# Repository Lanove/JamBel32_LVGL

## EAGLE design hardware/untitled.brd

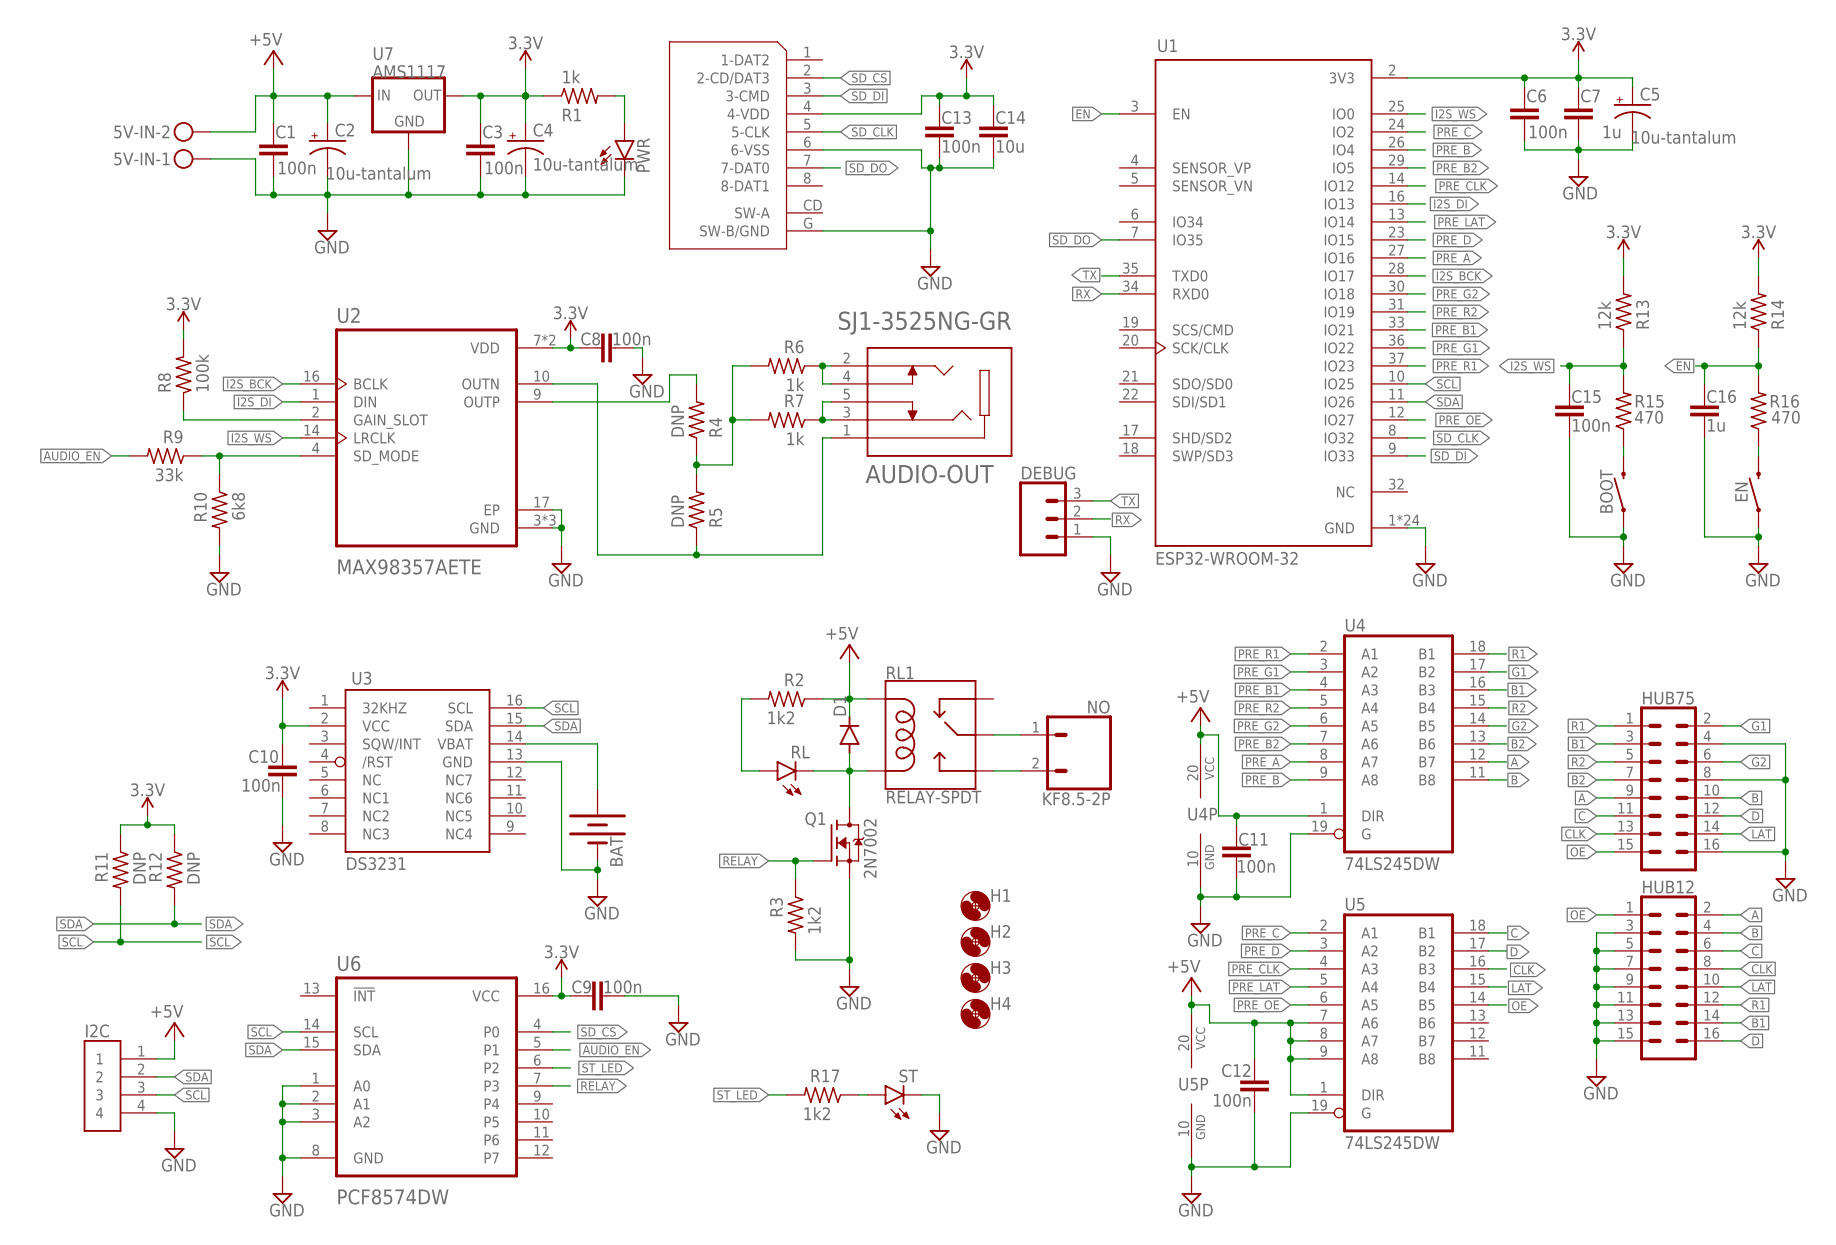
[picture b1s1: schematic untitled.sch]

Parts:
5V-IN: MKDSN1,5/2-5,08
AUDIO-OUT: SJ1-3525NG-GR; CUI_SJ1-3525NG-GR
BAT: BATTERY-20MM_PTH_KIT; BATTCOM_20MM_PTH_KIT
BOOT: MOMENTARY-SWITCH-SPST-SMD-6.0X3.5MM; TACTILE_SWITCH_SMD_6.0X3.5MM
C1, C3, C6, C8, C9, C10, C11, C12, C13, C15: 100n; C0603K
C2, C4, C5: 10u-tantalum; CT3528
C7, C16: 1u; C0603K
C14: 10u; C0603K
D1: DIODE-DO-214AC; DO-214AC
DEBUG: CONN_03; 1X03
EN: MOMENTARY-SWITCH-SPST-SMD-6.0X3.5MM; TACTILE_SWITCH_SMD_6.0X3.5MM
H1, H2, H3, H4: MOUNT-HOLE3.2; 3,2
HUB12, HUB75: CONN_08X2_SHROUD; 2X8-SHROUDED_LOCK
I2C: B4B-XH-A(LF)(SN); JST_B4B-XH-A(LF)(SN)
NO: KF8.5-2P; KF7.62
PWR: LEDCHIP-LED0805; CHIP-LED0805
Q1: 2N7002; SOT95P240X111-3N
R1, R6, R7: 1k; R0603
R2, R3, R17: 1k2; R0603
R4, R5, R11, R12: DNP; R0603
R8: 100k; R0603
R9: 33k; R0603
R10: 6k8; R0603
R13, R14: 12k; R0603
R15, R16: 470; R0603
RL: LEDCHIP-LED0805; CHIP-LED0805
RL1: RELAY-SPDT; RELAY_G5LE
ST: LEDCHIP-LED0805; CHIP-LED0805
U1: ESP32-WROOM-32; MODULE_ESP32-WROOM-32
U2: MAX98357AETE; QFN50P300X300X80-17N
U3: DS3231/SO; SO16W
U4, U5: 74LS245DW; SO20W
U6: PCF8574DW; SOIC127P1030X265-16N
U7: AMS1117; SOT89R
μSD: 112J-TDAR-R01

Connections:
3.3V: C3.1, C4.+, C5.+, C6.1, C7.1, C8.1, C9.1, C10.2, C13.2, C14.2, R1.1, R8.2, R11.1, R12.1, R13.2, R14.2, U1.2 (3V3), U2.7 (VDD), U2.8 (VDD), U3.2 (VCC), U6.16 (VCC), U7.3 (OUT), U7.4 (OUT), μSD.4 (4-VDD)
+5V: 5V-IN.2, C1.1, C2.+, C11.1, C12.2, D1.C, I2C.1, R2.1, RL1.2 (COIL1), U4.1 (DIR), U4.20 (VCC), U5.1 (DIR), U5.7 (A6), U5.8 (A7), U5.9 (A8), U5.20 (VCC), U7.1 (IN)
A: HUB12.2, HUB75.9, U4.12 (B7)
AUDIO_EN: R9.2, U6.5 (P1)
B: HUB12.4, HUB75.10, U4.11 (B8)
B1: HUB12.14, HUB75.3, U4.16 (B3)
B2: HUB75.7, U4.13 (B6)
C: HUB12.6, HUB75.11, U5.18 (B1)
CLK: HUB12.8, HUB75.13, U5.16 (B3)
D: HUB12.16, HUB75.12, U5.17 (B2)
EN: C16.2, R14.1, R16.2, U1.3 (EN)
G1: HUB75.2, U4.17 (B2)
G2: HUB75.6, U4.14 (B5)
GND: 5V-IN.1, BAT.2 (-), BOOT.1, C1.2, C2.-, C3.2, C4.-, C5.-, C6.2, C7.2, C8.2, C9.2, C10.1, C11.2, C12.1, C13.1, C14.1, C15.1, C16.1, DEBUG.1, EN.1, HUB12.3, HUB12.5, HUB12.7, HUB12.9, HUB12.11, HUB12.13, HUB12.15, HUB75.4, HUB75.8, HUB75.16, I2C.4, PWR.C, Q1.2 (S), R3.2, R10.2, ST.C, U1.1 (GND), U1.15 (GND), U1.38 (GND), U1.39_1 (GND), U1.39_2 (GND), U1.39_3 (GND), U1.39_4 (GND), U1.39_5 (GND), U1.39_6 (GND), U1.39_7 (GND), U1.39_8 (GND), U1.39_9 (GND), U1.39_10 (GND), U1.39_11 (GND), U1.39_12 (GND), U1.39_13 (GND), U1.39_14 (GND), U1.39_15 (GND), U1.39_16 (GND), U1.39_17 (GND), U1.39_18 (GND), U1.39_19 (GND), U1.39_20 (GND), U1.39_21 (GND), U2.3 (GND), U2.11 (GND), U2.15 (GND), U2.17 (EP), U3.13 (GND), U4.10 (GND), U4.19 (G), U5.10 (GND), U5.19 (G), U6.1 (A0), U6.2 (A1), U6.3 (A2), U6.8 (GND), U7.2 (GND), μSD.6 (6-VSS), μSD.G (SW-B/GND)
I2S_BCK: U1.28 (IO17), U2.16 (BCLK)
I2S_DI: U1.16 (IO13), U2.1 (DIN)
I2S_WS: C15.2, R13.1, R15.2, U1.25 (IO0), U2.14 (LRCLK)
LAT: HUB12.10, HUB75.14, U5.15 (B4)
unnamed: NO.1, RL1.1 (MAIN)
unnamed: NO.2, RL1.3 (NO)
unnamed: R4.2, U2.9 (OUTP)
unnamed: PWR.A, R1.2
unnamed: AUDIO-OUT.1, R5.1, U2.10 (OUTN)
unnamed: R4.1, R5.2, R6.2, R7.2
unnamed: R8.1, U2.2 (GAIN_SLOT)
unnamed: AUDIO-OUT.3, AUDIO-OUT.5, R7.1
unnamed: R9.1, R10.1, U2.4 (SD_MODE)
unnamed: AUDIO-OUT.2, AUDIO-OUT.4, R6.1
unnamed: BAT.1 (+), U3.14 (VBAT)
unnamed: EN.2, R16.1
unnamed: BOOT.2, R15.1
unnamed: R17.1, ST.A
unnamed: D1.A, Q1.3 (D), RL.C, RL1.5 (COIL2)
unnamed: R2.2, RL.A
OE: HUB12.1, HUB75.15, U5.14 (B5)
PRE_A: U1.27 (IO16), U4.8 (A7)
PRE_B: U1.26 (IO4), U4.9 (A8)
PRE_B1: U1.33 (IO21), U4.4 (A3)
PRE_B2: U1.29 (IO5), U4.7 (A6)
PRE_C: U1.24 (IO2), U5.2 (A1)
PRE_CLK: U1.14 (IO12), U5.4 (A3)
PRE_D: U1.23 (IO15), U5.3 (A2)
PRE_G1: U1.36 (IO22), U4.3 (A2)
PRE_G2: U1.30 (IO18), U4.6 (A5)
PRE_LAT: U1.13 (IO14), U5.5 (A4)
PRE_OE: U1.12 (IO27), U5.6 (A5)
PRE_R1: U1.37 (IO23), U4.2 (A1)
PRE_R2: U1.31 (IO19), U4.5 (A4)
R1: HUB12.12, HUB75.1, U4.18 (B1)
R2: HUB75.5, U4.15 (B4)
RELAY: Q1.1 (G), R3.1, U6.7 (P3)
RX: DEBUG.2, U1.34 (RXD0)
SCL: I2C.3, R11.2, U1.10 (IO25), U3.16 (SCL), U6.14 (SCL)
SDA: I2C.2, R12.2, U1.11 (IO26), U3.15 (SDA), U6.15 (SDA)
SD_CLK: U1.8 (IO32), μSD.5 (5-CLK)
SD_CS: U6.4 (P0), μSD.2 (2-CD/DAT3)
SD_DI: U1.9 (IO33), μSD.3 (3-CMD)
SD_DO: U1.7 (IO35), μSD.7 (7-DAT0)
ST_LED: R17.2, U6.6 (P2)
TX: DEBUG.3, U1.35 (TXD0)

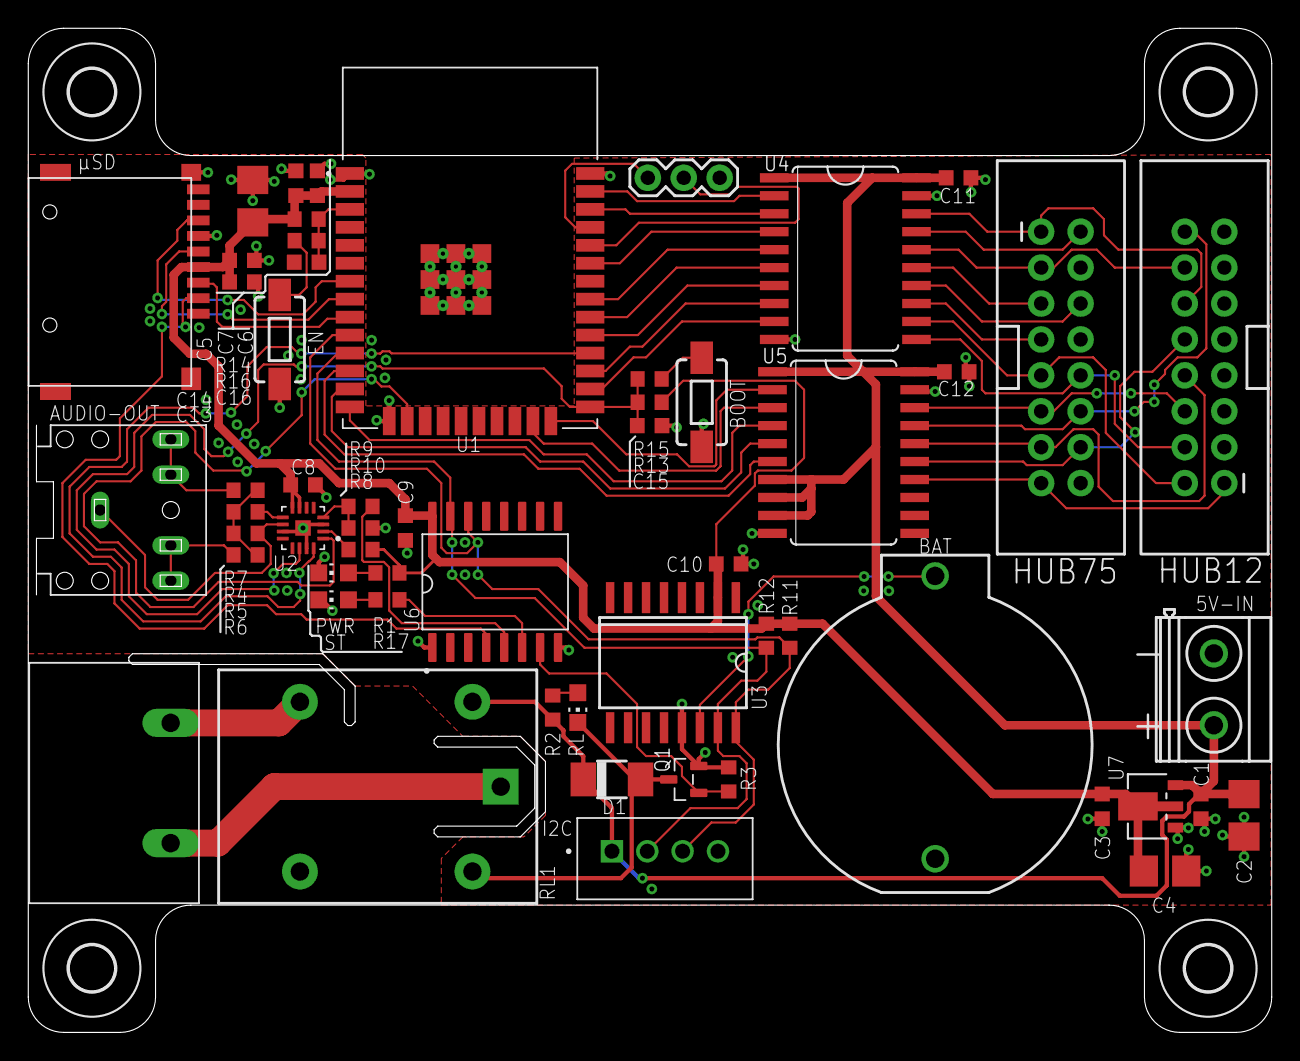
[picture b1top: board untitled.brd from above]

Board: 2 copper layers, 87.9 x 71.0 mm, 61 parts (0 on the bottom side), 60 nets.

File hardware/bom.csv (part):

"Part";"Value";"Device";"Package";"Description";"AVAILABILITY";"CUI_PURCHASE_URL";"DESCRIPTION";"MANUFACTURER";"MAXIMUM_PACKAGE_HEIGHT";"MF";"MP";"PACKAGE";"PARTREV";"POPULARITY";"PRICE";"PROD_ID";"PURCHASE-URL";"SF_SKU";"SPICEPREFIX";"STANDARD";"VALUE";
"5V-IN";"";"MKDSN1,5/2-5,08";"MKDSN1,5/2-5,08";"MKDSN 1,5/ 2-5,08 Printklemme";"";"";"";"";"";"";"";"";"";"14";"";"";"";"";"";"";"";
"AUDIO-OUT";"SJ1-3525NG-GR";"SJ1-3525NG-GR";"CUI_SJ1-3525NG-GR";"3.5 mm Right-Angle Stereo Jack, 5 Pin PCB Mount, Isolated Ground, Green Check availability";"In Stock";"https://www.cuidevices.com/product/interconnect/connectors/a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";"3.5 mm, Stereo, Right Angle, Through Hole, Isolated Ground, 3 Conductors, 0~2 Internal Switches, Audio Jack Connector";"";"";"CUI Devices";"SJ1-3525NG-GR";"None";"";"";"None";"";"https://pricing.snapeda.com/search/part/SJ1-3525NG-GR/?ref=eda";"";"";"";"";
"BAT";"";"BATTERY-20MM_PTH_KIT";"BATTCOM_20MM_PTH_KIT";"Battery - Single Cell";"";"";"";"";"";"";"";"";"";"";"";"";"";"";"";"";"";
"BOOT";"";"MOMENTARY-SWITCH-SPST-SMD-6.0X3.5MM";"TACTILE_SWITCH_SMD_6.0X3.5MM";"Momentary Switch (Pushbutton) - SPST";"";"";"";"";"";"";"";"";"";"";"";"SWCH-14278";"";"COM-08229";"";"";"";
"C1";"100n";"C-EUC0603K";"C0603K";"CAPACITOR, European symbol";"";"";"";"";"";"";"";"";"";"30";"";"";"";"";"C";"";"";
"C2";"10u-tantalum";"CPOL-USCT3528";"CT3528";"POLARIZED CAPACITOR, American symbol";"";"";"";"";"";"";"";"";"";"2";"";"";"";"";"C";"";"";
"C3";"100n";"C-EUC0603K";"C0603K";"CAPACITOR, European symbol";"";"";"";"";"";"";"";"";"";"30";"";"";"";"";"C";"";"";
"C4";"10u-tantalum";"CPOL-USCT3528";"CT3528";"POLARIZED CAPACITOR, American symbol";"";"";"";"";"";"";"";"";"";"2";"";"";"";"";"C";"";"";
"C5";"10u-tantalum";"CPOL-USCT3528";"CT3528";"POLARIZED CAPACITOR, American symbol";"";"";"";"";"";"";"";"";"";"2";"";"";"";"";"C";"";"";
"C6";"100n";"C-EUC0603K";"C0603K";"CAPACITOR, European symbol";"";"";"";"";"";"";"";"";"";"30";"";"";"";"";"C";"";"";
"C7";"1u";"C-EUC0603K";"C0603K";"CAPACITOR, European symbol";"";"";"";"";"";"";"";"";"";"30";"";"";"";"";"C";"";"";
"C8";"100n";"C-EUC0603K";"C0603K";"CAPACITOR, European symbol";"";"";"";"";"";"";"";"";"";"30";"";"";"";"";"C";"";"";
"C9";"100n";"C-EUC0603K";"C0603K";"CAPACITOR, European symbol";"";"";"";"";"";"";"";"";"";"30";"";"";"";"";"C";"";"";
"C10";"100n";"C-EUC0603K";"C0603K";"CAPACITOR, European symbol";"";"";"";"";"";"";"";"";"";"30";"";"";"";"";"C";"";"";
"C11";"100n";"C-EUC0603K";"C0603K";"CAPACITOR, European symbol";"";"";"";"";"";"";"";"";"";"30";"";"";"";"";"C";"";"";
"C12";"100n";"C-EUC0603K";"C0603K";"CAPACITOR, European symbol";"";"";"";"";"";"";"";"";"";"30";"";"";"";"";"C";"";"";
"C13";"100n";"C-EUC0603K";"C0603K";"CAPACITOR, European symbol";"";"";"";"";"";"";"";"";"";"30";"";"";"";"";"C";"";"";
"C14";"10u";"C-EUC0603K";"C0603K";"CAPACITOR, European symbol";"";"";"";"";"";"";"";"";"";"30";"";"";"";"";"C";"";"";
"C15";"100n";"C-EUC0603K";"C0603K";"CAPACITOR, European symbol";"";"";"";"";"";"";"";"";"";"30";"";"";"";"";"C";"";"";
"C16";"1u";"C-EUC0603K";"C0603K";"CAPACITOR, European symbol";"";"";"";"";"";"";"";"";"";"30";"";"";"";"";"C";"";"";
"D1";"";"DIODE-DO-214AC";"DO-214AC";"DIODE";"";"";"";"";"";"";"";"";"";"25";"";"";"";"";"";"";"";
"DEBUG";"";"CONN_03";"1X03";"Multi connection point. Often used as Generic Header-pin footprint for 0.1 inch spaced/style header connections";"";"";"";"";"";"";"";"";"";"";"";"XXX-00000";"";"";"";"";"455-1750-1-ND";
"EN";"";"MOMENTARY-SWITCH-SPST-SMD-6.0X3.5MM";"TACTILE_SWITCH_SMD_6.0X3.5MM";"Momentary Switch (Pushbutton) - SPST";"";"";"";"";"";"";"";"";"";"";"";"SWCH-14278";"";"COM-08229";"";"";"";
"H1";"";"MOUNT-HOLE3.2";"3,2";"MOUNTING HOLE with drill center marker";"";"";"";"";"";"";"";"";"";"7";"";"";"";"";"";"";"";
"H2";"";"MOUNT-HOLE3.2";"3,2";"MOUNTING HOLE with drill center marker";"";"";"";"";"";"";"";"";"";"7";"";"";"";"";"";"";"";
"H3";"";"MOUNT-HOLE3.2";"3,2";"MOUNTING HOLE with drill center marker";"";"";"";"";"";"";"";"";"";"7";"";"";"";"";"";"";"";
"H4";"";"MOUNT-HOLE3.2";"3,2";"MOUNTING HOLE with drill center marker";"";"";"";"";"";"";"";"";"";"7";"";"";"";"";"";"";"";
"HUB12";"";"CONN_08X2_SHROUD";"2X8-SHROUDED_LOCK";"Multi connection point. Often used as Generic Header-pin footprint for 0.1 inch spaced/style header connections";"";"";"";"";"";"";"";"";"";"";"";"";"";"";"";"";"";
"HUB75";"";"CONN_08X2_SHROUD";"2X8-SHROUDED_LOCK";"Multi connection point. Often used as Generic Header-pin footprint for 0.1 inch spaced/style header connections";"";"";"";"";"";"";"";"";"";"";"";"";"";"";"X";"";"";
"I2C";"";"B4B-XH-A(LF)(SN)";"JST_B4B-XH-A(LF)(SN)";"XH Series 4 Position 2.5 mm Pitch Through Hole Crimp Top Entry Shrouded Header";"";"";"";" JST Sales America Inc";"";"";"";"";"NA";"";"";"";"";"";"";"Manufacturer Recommendation";"";
"NO";"KF8.5-2P";"KF7.62-2P";"KF7.62";"";"";"";"";"";"";"";"";"";"";"";"";"";"";"";"";"";"";
"PWR";"";"LEDCHIP-LED0805";"CHIP-LED0805";"LED";"";"";"";"";"";"";"";"";"";"68";"";"";"";"";"";"";"";
"Q1";"2N7002";"2N7002";"SOT95P240X111-3N";"N-Channel 60V 280mA (Ta) 350mW (Ta) Surface Mount SOT-23-3 (TO-236)  Check availability";"In Stock";"";" N-Channel 60V 280mA (Ta) 350mW (Ta) Surface Mount SOT-23-3 (TO-236) ";"";"";"ON Semiconductor";"2N7002";"SOT-23-3 ON Semiconductor";"";"";"None";"";"https://pricing.snapeda.com/search/part/2N7002/?ref=eda";"";"";"";"";
"R1";"1k";"R-US_R0603";"R0603";"RESISTOR, American symbol";"";"";"";"";"";"";"";"";"";"77";"";"";"";"";"R";"";"";
"R2";"1k2";"R-US_R0603";"R0603";"RESISTOR, American symbol";"";"";"";"";"";"";"";"";"";"77";"";"";"";"";"R";"";"";
"R3";"1k2";"R-US_R0603";"R0603";"RESISTOR, American symbol";"";"";"";"";"";"";"";"";"";"77";"";"";"";"";"R";"";"";
"R4";"DNP";"R-US_R0603";"R0603";"RESISTOR, American symbol";"";"";"";"";"";"";"";"";"";"77";"";"";"";"";"R";"";"";
"R5";"DNP";"R-US_R0603";"R0603";"RESISTOR, American symbol";"";"";"";"";"";"";"";"";"";"77";"";"";"";"";"R";"";"";
"R6";"1k";"R-US_R0603";"R0603";"RESISTOR, American symbol";"";"";"";"";"";"";"";"";"";"77";"";"";"";"";"R";"";"";
"R7";"1k";"R-US_R0603";"R0603";"RESISTOR, American symbol";"";"";"";"";"";"";"";"";"";"77";"";"";"";"";"R";"";"";
"R8";"100k";"R-US_R0603";"R0603";"RESISTOR, American symbol";"";"";"";"";"";"";"";"";"";"77";"";"";"";"";"R";"";"";
"R9";"33k";"R-US_R0603";"R0603";"RESISTOR, American symbol";"";"";"";"";"";"";"";"";"";"77";"";"";"";"";"R";"";"";
"R10";"6k8";"R-US_R0603";"R0603";"RESISTOR, American symbol";"";"";"";"";"";"";"";"";"";"77";"";"";"";"";"R";"";"";
"R11";"DNP";"R-US_R0603";"R0603";"RESISTOR, American symbol";"";"";"";"";"";"";"";"";"";"77";"";"";"";"";"R";"";"";
"R12";"DNP";"R-US_R0603";"R0603";"RESISTOR, American symbol";"";"";"";"";"";"";"";"";"";"77";"";"";"";"";"R";"";"";
"R13";"12k";"R-US_R0603";"R0603";"RESISTOR, American symbol";"";"";"";"";"";"";"";"";"";"77";"";"";"";"";"R";"";"";
"R14";"12k";"R-US_R0603";"R0603";"RESISTOR, American symbol";"";"";"";"";"";"";"";"";"";"77";"";"";"";"";"R";"";"";
"R15";"470";"R-US_R0603";"R0603";"RESISTOR, American symbol";"";"";"";"";"";"";"";"";"";"77";"";"";"";"";"R";"";"";
"R16";"470";"R-US_R0603";"R0603";"RESISTOR, American symbol";"";"";"";"";"";"";"";"";"";"77";"";"";"";"";"R";"";"";
"R17";"1k2";"R-US_R0603";"R0603";"RESISTOR, American symbol";"";"";"";"";"";"";"";"";"";"77";"";"";"";"";"R";"";"";
"RL";"";"LEDCHIP-LED0805";"CHIP-LED0805";"LED";"";"";"";"";"";"";"";"";"";"68";"";"";"";"";"";"";"";
"RL1";"RELAY-SPDT";"RELAY-SPDT";"RELAY_G5LE";"SPDT Electromechanical Relay";"";"";"";"";"";"";"";"";"";"";"";"COMP-14214";"";"";"";"";"";
"ST";"";"LEDCHIP-LED0805";"CHIP-LED0805";"LED";"";"";"";"";"";"";"";"";"";"68";"";"";"";"";"";"";"";
"U1";"ESP32-WROOM-32";"ESP32-WROOM-32";"MODULE_ESP32-WROOM-32";"";"";"";"";"Espressif Systems";"3.2 mm";"";"";"";"2.9";"";"";"";"";"";"";"Manufacturer Recommendations";"";
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
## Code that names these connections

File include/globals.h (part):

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#define I2S_MIN_GAIN 0.016
#define I2S_VOLUME_STEP 10.
#define I2S_DO GPIO_NUM_13
#define I2S_BCK GPIO_NUM_17
#define I2S_WS GPIO_NUM_0

#define IOEXPAND_I2C_ADDRESS 0x20
#define I2C_SDA GPIO_NUM_26
#define I2C_SCL GPIO_NUM_25
#define I2C_FREQ 100000U

#define SD_DI GPIO_NUM_33
#define SD_DO GPIO_NUM_35
#define SD_CS GPIO_NUM_14
#define SD_CLK GPIO_NUM_32
#define SDSPI_FREQUENCY 16000000U

LV_FONT_DECLARE(Montserrat_SemiBold91)
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
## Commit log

2022-05-16 Init port
2022-05-16 UI/UX working, espsys is on SD
2022-05-16 Audio worked
2022-05-16 Release 1.00
2022-05-20 Removed struct belManual member buttonPointer
2022-05-21 Changed LV memory reserve to 64K Traverser now only list directory and mp3 files only
2022-05-21 Added firmware update via SD Card Added serial eFuseMAC print command
2022-05-23 fixed rmdir() problem
2022-05-23 I2S_EN is now always HIGH, to avoid buzzing Added images of the project
2022-05-23 Fixed buzzing problem when audio is not yet played after boot
2022-05-27 Fixed bug, JadwalHari not loaded on first bel of the day Added hardware files

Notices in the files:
parts and their libraries:
SparkFun-Batteries: Licensing: Creative Commons ShareAlike 4.0 International - https://creativecommons.org/licenses/by-sa/4.0
